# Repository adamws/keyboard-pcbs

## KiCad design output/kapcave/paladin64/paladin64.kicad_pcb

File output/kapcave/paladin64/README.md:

## kapcave/paladin64

[layout](paladin64-kle.json) - [PCB](paladin64.kicad_pcb)

{:loading="lazy"}

[Open in keyboard-layout-editor](http://www.keyboard-layout-editor.com/##@@_x:3&c=#777777;&=3,6&_c=#cccccc;&=3,7&=4,6&=4,7&=5,6&=5,7&=6,6&=6,7&=7,6&=7,7&=0,6&=0,7&=1,7&_c=#aaaaaa&w:2;&=2,7%0A%0A%0A0,0;&@_x:3&w:1.5;&=3,4&_c=#cccccc;&=3,5&=4,4&=4,5&=5,4&=5,5&=6,4&=6,5&=7,5&=0,5&=1,5&=1,6&=2,5&_c=#aaaaaa&w:1.5;&=2,4;&@_x:3.0&w:1.75;&=3,2%0A%0A%0A1,0&_c=#cccccc;&=3,3&=4,3&=5,2&=5,3&=6,3&=7,3&=7,4&=0,3&=0,4&=1,3&=1,4&_c=#777777&w:2.25;&=2,3%0A%0A%0A4,0;&@_x:3.0&c=#aaaaaa&w:2.25;&=3,1%0A%0A%0A2,0&_c=#cccccc;&=4,2&=5,1&=6,1&=6,2&=7,1&=7,2&=0,1&=0,2&=1,1&=1,2&_c=#aaaaaa&w:2.75;&=2,1%0A%0A%0A3,0;&@_x:3&w:1.5;&=3,0%0A%0A%0A5,0&_w:1.25;&=4,0%0A%0A%0A5,0&_w:1.5;&=5,0%0A%0A%0A5,0&_w:6.5;&=6,0%0A%0A%0A5,0&_w:1.5;&=0,0%0A%0A%0A5,0&_w:1.25;&=1,0%0A%0A%0A5,0&_w:1.5;&=2,0%0A%0A%0A5,0;&@_x:19.25&y:-5&c=#cccccc;&=2,6%0A%0A%0A0,1&_c=#aaaaaa;&=2,7%0A%0A%0A0,1;&@_x:20.0&c=#777777&w:1.25&h:2&w2:1.5&h2:1&x2:-0.25;&=2,3%0A%0A%0A4,1&_x:1.5&w:1.5&h:2&w2:2.25&h2:1&x2:-0.75&y2:1;&=2,3%0A%0A%0A4,2;&@_c=#aaaaaa&w:1.25&w2:1.75&l:true;&=3,2%0A%0A%0A1,1&_x:17.75&c=#cccccc;&=2,4%0A%0A%0A4,1;&@_c=#aaaaaa&w:1.25;&=3,1%0A%0A%0A2,1&_c=#cccccc;&=4,1%0A%0A%0A2,1&_x:16.25&c=#aaaaaa&w:1.75;&=2,1%0A%0A%0A3,1&_c=#cccccc;&=2,2%0A%0A%0A3,1&_x:0.25;&=2,2%0A%0A%0A3,2&_c=#aaaaaa&w:1.75;&=2,1%0A%0A%0A3,2;&@_x:3&y:1.5&w:1.5;&=3,0%0A%0A%0A5,1&=4,0%0A%0A%0A5,1&_w:1.5;&=5,0%0A%0A%0A5,1&_w:7;&=6,0%0A%0A%0A5,1&_w:1.5;&=0,0%0A%0A%0A5,1&=1,0%0A%0A%0A5,1&_w:1.5;&=2,0%0A%0A%0A5,1;&@_x:3&w:1.25;&=3,0%0A%0A%0A5,2&_w:1.25;&=4,0%0A%0A%0A5,2&_w:1.25;&=5,0%0A%0A%0A5,2&_w:6.25;&=6,0%0A%0A%0A5,2&_w:1.25;&=7,0%0A%0A%0A5,2&_w:1.25;&=0,0%0A%0A%0A5,2&_w:1.25;&=1,0%0A%0A%0A5,2&_w:1.25;&=2,0%0A%0A%0A5,2;&@_x:3&w:1.5;&=3,0%0A%0A%0A5,3&=4,0%0A%0A%0A5,3&_w:1.5;&=5,0%0A%0A%0A5,3&_w:6;&=6,0%0A%0A%0A5,3&_w:1.5;&=7,0%0A%0A%0A5,3&=0,0%0A%0A%0A5,3&=1,0%0A%0A%0A5,3&_w:1.5;&=2,0%0A%0A%0A5,3;&@_x:3&w:1.25;&=3,0%0A%0A%0A5,4&_w:1.25&d:true;&=3,0%0A%0A%0A5,4&=4,0%0A%0A%0A5,4&_w:1.75;&=5,0%0A%0A%0A5,4&_w:3;&=6,0%0A%0A%0A5,4&_w:1.75;&=7,0%0A%0A%0A5,4&_w:1.25&d:true;&=7,0%0A%0A%0A5,4&_w:1.25;&=0,0%0A%0A%0A5,4&_w:1.25;&=1,0%0A%0A%0A5,4&_w:1.25;&=2,0%0A%0A%0A5,4)

{:loading="lazy"}

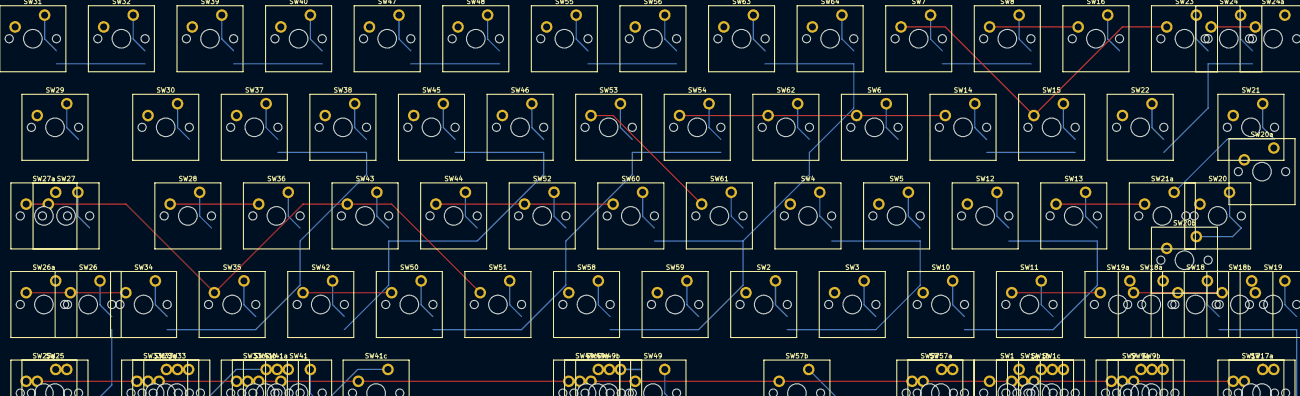
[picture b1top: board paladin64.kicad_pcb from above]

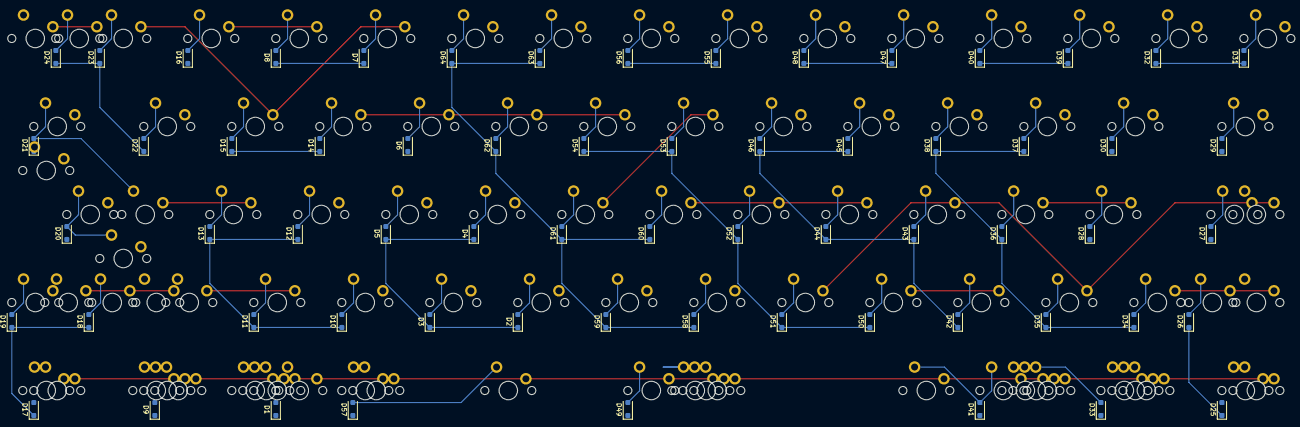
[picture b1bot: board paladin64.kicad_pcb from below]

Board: 2 copper layers, 155 parts (64 on the bottom side), 80 nets.

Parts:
D1, D2, D3, D4, D5, D6, D7, D8, D9, D10, D11, D12, D13, D14, D15, D16, D17, D18, D19, D20, D21, D22, D23, D24, D25, D26, D27, D28, D29, D30, D31, D32, D33, D34, D35, D36, D37, D38, D39, D40, D41, D42, D43, D44, D45, D46, D47, D48, D49, D50, D51, D52, D53, D54, D55, D56, D57, D58, D59, D60, D61, D62, D63, D64: D_SOD-123F
SW1, SW1a, SW1b, SW1c, SW2, SW3, SW4, SW5, SW6, SW7, SW8, SW9, SW9a, SW9b, SW10, SW11, SW12, SW13, SW14, SW15, SW16, SW17, SW17a, SW18, SW18a, SW18b, SW19, SW19a, SW20, SW20a, SW20b, SW21, SW21a, SW22, SW23, SW24, SW24a, SW25, SW25a, SW26, SW26a, SW27, SW27a, SW28, SW29, SW30, SW31, SW32, SW33, SW33a, SW33b, SW33c, SW34, SW35, SW36, SW37, SW38, SW39, SW40, SW41, SW41a, SW41b, SW41c, SW42, SW43, SW44, SW45, SW46, SW47, SW48, SW49, SW49a, SW49b, SW49c, SW50, SW51, SW52, SW53, SW54, SW55, SW56, SW57, SW57a, SW57b, SW58, SW59, SW60, SW61, SW62, SW63, SW64: SW_Cherry_MX_PCB_1.00u

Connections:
COL0: SW1.1, SW1a.1, SW1b.1, SW1c.1, SW9.1, SW9a.1, SW9b.1, SW17.1, SW17a.1, SW25.1, SW25a.1, SW33.1, SW33a.1, SW33b.1, SW33c.1, SW41.1, SW41a.1, SW41b.1, SW41c.1, SW49.1, SW49a.1, SW49b.1, SW49c.1, SW57.1, SW57a.1, SW57b.1
COL1: SW2.1, SW10.1, SW18.1, SW18a.1, SW18b.1, SW26.1, SW26a.1, SW34.1, SW42.1, SW50.1, SW58.1
COL2: SW3.1, SW11.1, SW19.1, SW19a.1, SW27.1, SW27a.1, SW35.1, SW43.1, SW51.1, SW59.1
COL3: SW4.1, SW12.1, SW20.1, SW20a.1, SW20b.1, SW28.1, SW36.1, SW44.1, SW52.1, SW60.1
COL4: SW5.1, SW13.1, SW21.1, SW21a.1, SW29.1, SW37.1, SW45.1, SW53.1, SW61.1
COL5: SW6.1, SW14.1, SW22.1, SW30.1, SW38.1, SW46.1, SW54.1, SW62.1
COL6: SW7.1, SW15.1, SW23.1, SW31.1, SW39.1, SW47.1, SW55.1, SW63.1
COL7: SW8.1, SW16.1, SW24.1, SW24a.1, SW32.1, SW40.1, SW48.1, SW56.1, SW64.1
unnamed: D1.2, SW1.2, SW1a.2, SW1b.2, SW1c.2
unnamed: D2.2, SW2.2
unnamed: D3.2, SW3.2
unnamed: D4.2, SW4.2
unnamed: D5.2, SW5.2
unnamed: D6.2, SW6.2
unnamed: D7.2, SW7.2
unnamed: D8.2, SW8.2
unnamed: D9.2, SW9.2, SW9a.2, SW9b.2
unnamed: D10.2, SW10.2
unnamed: D11.2, SW11.2
unnamed: D12.2, SW12.2
unnamed: D13.2, SW13.2
unnamed: D14.2, SW14.2
unnamed: D15.2, SW15.2
unnamed: D16.2, SW16.2
unnamed: D17.2, SW17.2, SW17a.2
unnamed: D18.2, SW18.2, SW18a.2, SW18b.2
unnamed: D19.2, SW19.2, SW19a.2
unnamed: D20.2, SW20.2, SW20a.2, SW20b.2
unnamed: D21.2, SW21.2, SW21a.2
unnamed: D22.2, SW22.2
unnamed: D23.2, SW23.2
unnamed: D24.2, SW24.2, SW24a.2
unnamed: D25.2, SW25.2, SW25a.2
unnamed: D26.2, SW26.2, SW26a.2
unnamed: D27.2, SW27.2, SW27a.2
unnamed: D28.2, SW28.2
unnamed: D29.2, SW29.2
unnamed: D30.2, SW30.2
unnamed: D31.2, SW31.2
unnamed: D32.2, SW32.2
unnamed: D33.2, SW33.2, SW33a.2, SW33b.2, SW33c.2
unnamed: D34.2, SW34.2
unnamed: D35.2, SW35.2
unnamed: D36.2, SW36.2
unnamed: D37.2, SW37.2
unnamed: D38.2, SW38.2
unnamed: D39.2, SW39.2
unnamed: D40.2, SW40.2
unnamed: D41.2, SW41.2, SW41a.2, SW41b.2, SW41c.2
unnamed: D42.2, SW42.2
unnamed: D43.2, SW43.2
unnamed: D44.2, SW44.2
unnamed: D45.2, SW45.2
unnamed: D46.2, SW46.2
unnamed: D47.2, SW47.2
unnamed: D48.2, SW48.2
unnamed: D49.2, SW49.2, SW49a.2, SW49b.2, SW49c.2
unnamed: D50.2, SW50.2
unnamed: D51.2, SW51.2
unnamed: D52.2, SW52.2
unnamed: D53.2, SW53.2
unnamed: D54.2, SW54.2
unnamed: D55.2, SW55.2
unnamed: D56.2, SW56.2
unnamed: D57.2, SW57.2, SW57a.2, SW57b.2
unnamed: D58.2, SW58.2
unnamed: D59.2, SW59.2
unnamed: D60.2, SW60.2
unnamed: D61.2, SW61.2
unnamed: D62.2, SW62.2
unnamed: D63.2, SW63.2
unnamed: D64.2, SW64.2
ROW0: D1.1, D2.1, D3.1, D4.1, D5.1, D6.1, D7.1, D8.1
ROW1: D9.1, D10.1, D11.1, D12.1, D13.1, D14.1, D15.1, D16.1
ROW2: D17.1, D18.1, D19.1, D20.1, D21.1, D22.1, D23.1, D24.1
ROW3: D25.1, D26.1, D27.1, D28.1, D29.1, D30.1, D31.1, D32.1
ROW4: D33.1, D34.1, D35.1, D36.1, D37.1, D38.1, D39.1, D40.1
ROW5: D41.1, D42.1, D43.1, D44.1, D45.1, D46.1, D47.1, D48.1
ROW6: D49.1, D50.1, D51.1, D52.1, D53.1, D54.1, D55.1, D56.1
ROW7: D57.1, D58.1, D59.1, D60.1, D61.1, D62.1, D63.1, D64.1
